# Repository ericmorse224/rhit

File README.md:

Rose-Hulman Institute of Technology (RHIT) github contains all of the work, except ECE230 and ECE434 class, in individual branches within RHIT main branch.
I moved all branches into individual folders for better organization.

ECE230 folder is Embedded C code from Introduction to Embedded Systems class.

ECE310 folder is Matlab code from Communication Systems class.

ECE320 folder is Simulink and C code from Linear Controls class (some code was provided by professor to modify).

ECE333 folder is Verilog code from Embedded Systems class

ECE341 folder is Matlab code from Electromagnetic Fields class.

ECE380 folder is LabVIEW code from Discrete Time and Continuous Signals class.

MATLAB folder is Matlab code that I created while at Rose-Hulman.

PCB folder is PCB layout that I created at Rose-Hulman.

PspiceFiles folder is Orcad Pspice files that I created at Rose-Hulman.

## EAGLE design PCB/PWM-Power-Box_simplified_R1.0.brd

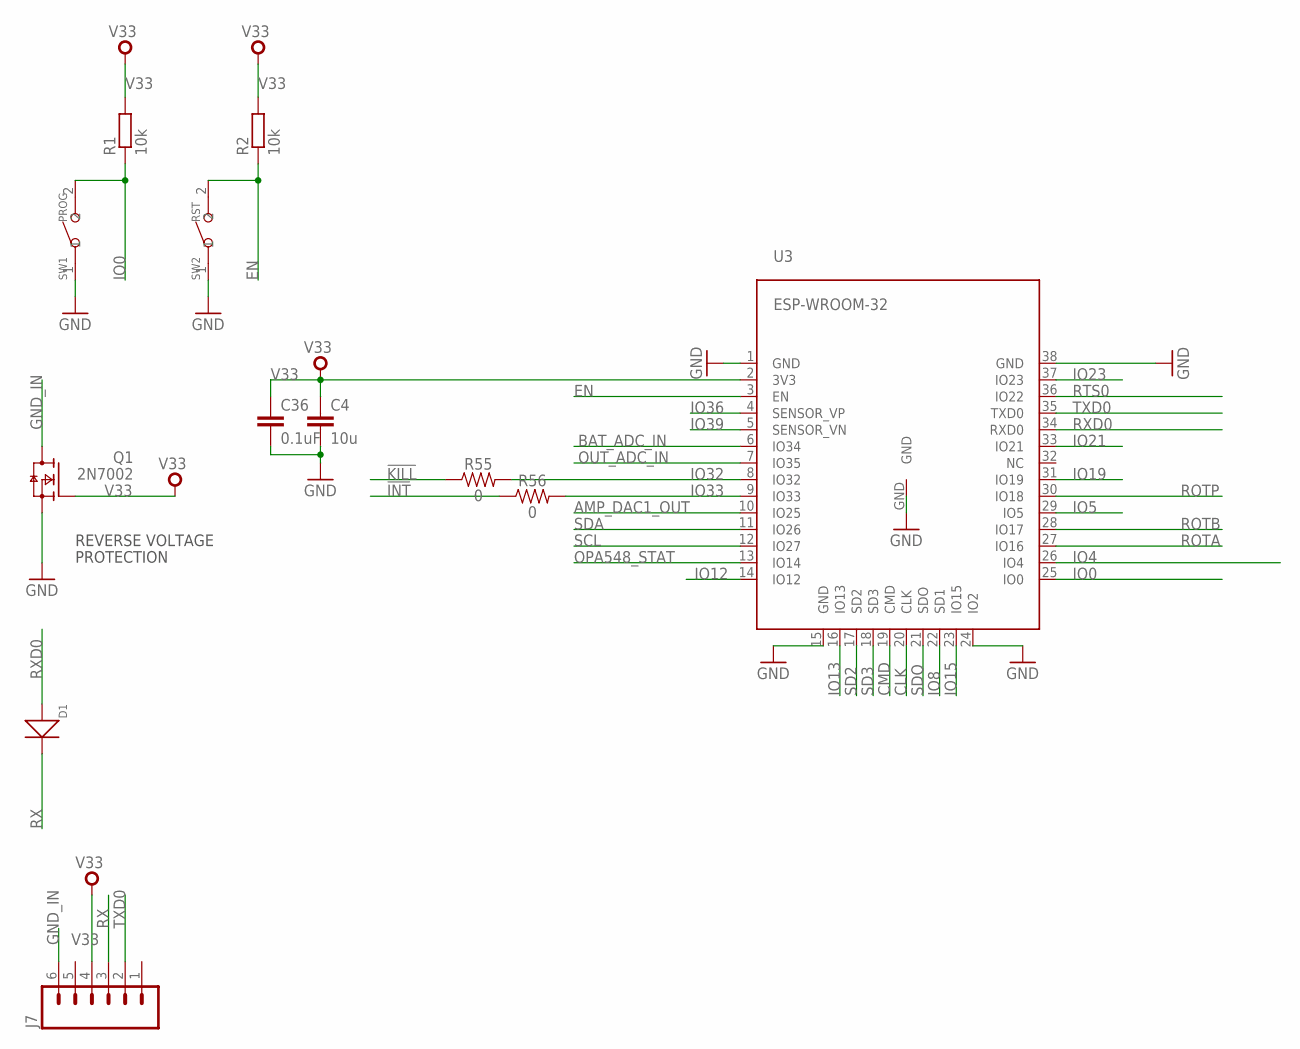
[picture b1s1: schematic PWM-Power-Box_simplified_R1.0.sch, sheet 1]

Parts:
C4: 10u; C0603
C36: 0.1uF; C0603
D1: DIODE'0805'; SOD-323
J7: M06SILK_FEMALE_PTH; 1X06
Q1: 2N7002; SOT23
R1, R2: 10k; R0603
R55, R56: 0; 0603
SW1: PROG; SW2-4.0-6.0X3.0X2.5MM
SW2: RST; SW2-4.0-6.0X3.0X2.5MM
U3: ESP-WROOM-32

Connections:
!INT: R56.1; also elsewhere on the board
!KILL: R55.1; also elsewhere on the board
AMP_DAC1_OUT: U3.10 (IO25); also elsewhere on the board
BAT_ADC_IN: U3.6 (IO34); also elsewhere on the board
CLK: U3.20 (CLK)
CMD: U3.19 (CMD)
EN: R2.1, SW2.2, U3.3 (EN); also elsewhere on the board
GND: C4.2, C36.2, Q1.2 (S), SW1.1, SW2.1, U3.1 (GND), U3.15 (GND), U3.24 (IO2), U3.38 (GND), U3.GND; also elsewhere on the board
GND_IN: J7.6, Q1.3 (D)
IO0: R1.1, SW1.2, U3.25 (IO0); also elsewhere on the board
IO4: U3.26 (IO4)
IO5: U3.29 (IO5)
IO8: U3.22 (SD1)
IO12: U3.14 (IO12)
IO13: U3.16 (IO13)
IO15: U3.23 (IO15)
IO19: U3.31 (IO19)
IO21: U3.33 (IO21)
IO23: U3.37 (IO23)
IO32: R55.2, U3.8 (IO32)
IO33: R56.2, U3.9 (IO33)
IO36: U3.4 (SENSOR_VP)
IO39: U3.5 (SENSOR_VN)
OPA548_STAT: U3.13 (IO14); also elsewhere on the board
OUT_ADC_IN: U3.7 (IO35); also elsewhere on the board
ROTA: U3.27 (IO16); also elsewhere on the board
ROTB: U3.28 (IO17); also elsewhere on the board
ROTP: U3.30 (IO18); also elsewhere on the board
RTS0: U3.36 (IO22)
RX: D1.-, J7.3
RXD0: D1.+, U3.34 (RXD0); also elsewhere on the board
SCL: U3.12 (IO27); also elsewhere on the board
SD2: U3.17 (SD2)
SD3: U3.18 (SD3)
SDA: U3.11 (IO26); also elsewhere on the board
SDO: U3.21 (SDO)
TXD0: J7.2, U3.35 (TXD0); also elsewhere on the board
V33: C4.1, C36.1, J7.4, Q1.1 (G), R1.2, R2.2, U3.2 (3V3); also elsewhere on the board

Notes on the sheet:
REVERSE VOLTAGE
PROTECTION

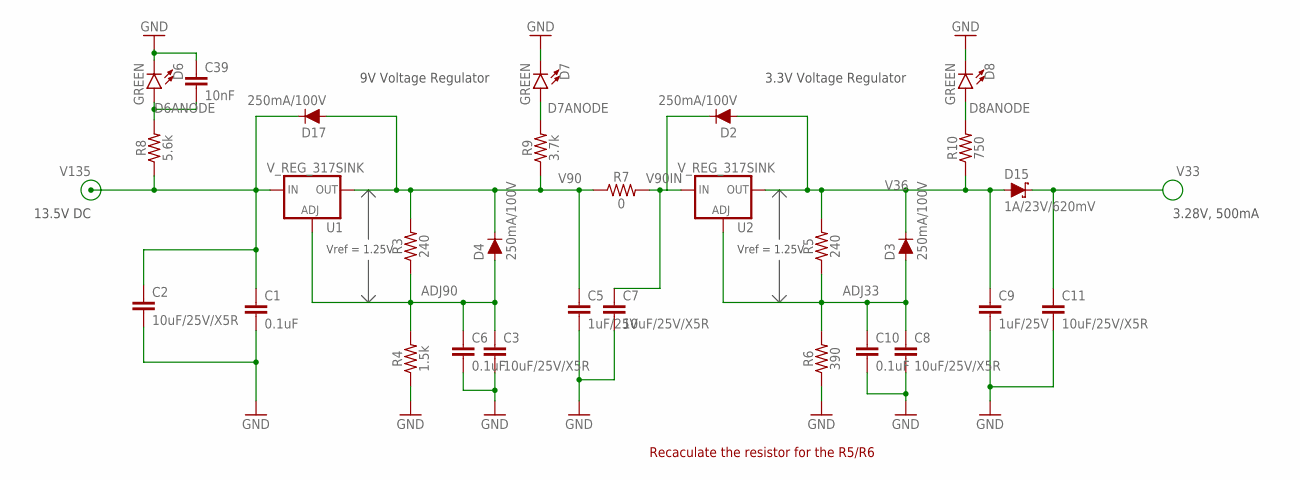
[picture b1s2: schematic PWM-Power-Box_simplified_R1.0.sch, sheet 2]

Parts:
C1: 0.1uF; C0805K
C2, C7, C11: 10uF/25V/X5R; C1210K
C3: 10uF/25V/X5R; C0805
C5, C9: 1uF/25V; C0805K
C6, C10: 0.1uF; C0603
C8: 10uF/25V/X5R; C0603
C39: 10nF; C0603
D2, D3, D4, D17: 250mA/100V; SOD-323
D6, D7, D8: GREEN; LED-0603
D15: 1A/23V/620mV; SOD-323
R3, R5: 240; 0603
R4: 1.5k; 0603
R6: 390; 0603
R7: 0; 1210
R8: 5.6k; 0603
R9: 3.7k; 0603
R10: 750; 0603
U1, U2: V_REG_317SINK; TO220-ADJ

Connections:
GND: C1.2, C2.2, C3.2, C5.2, C6.2, C7.2, C8.2, C9.2, C10.2, C11.2, C39.1, D6.C, D7.C, D8.C, R4.1, R6.1; also elsewhere on the board
unnamed: C3.1, C6.1, D4.A, R3.1, R4.2, U1.ADJ
unnamed: C8.1, C10.1, D3.A, R5.1, R6.2, U2.ADJ
unnamed: C7.1, D2.C, R7.2, U2.IN
unnamed: C39.2, D6.A, R8.2
unnamed: D7.A, R9.2
unnamed: D8.A, R10.2
V33: C11.1, D15.C; also elsewhere on the board
V36: C9.1, D2.A, D3.C, D15.A, R5.2, R10.1, U2.OUT
V90: C5.1, D4.C, D17.A, R3.2, R7.1, R9.1, U1.OUT
V135: C1.1, C2.1, D17.C, R8.1, U1.IN; also elsewhere on the board

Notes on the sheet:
9V Voltage Regulator
13.5V DC
Vref = 1.25V
3.3V Voltage Regulator
3.28V, 500mA
Recaculate the resistor for the R5/R6

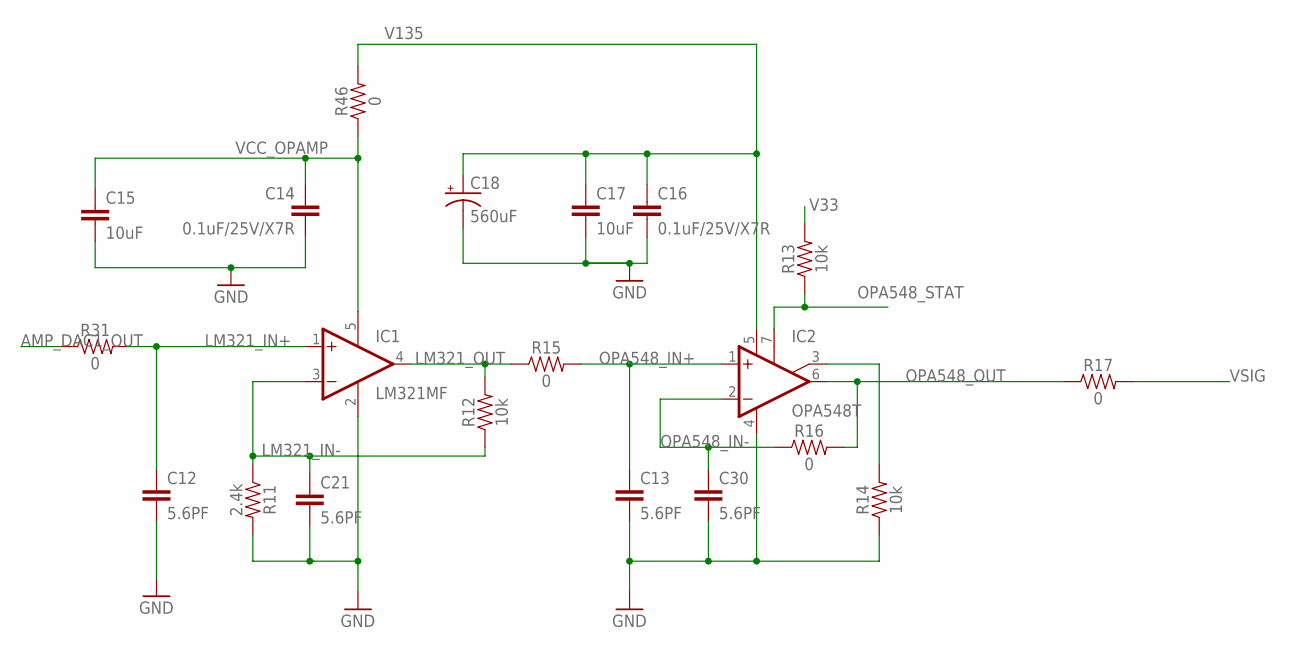
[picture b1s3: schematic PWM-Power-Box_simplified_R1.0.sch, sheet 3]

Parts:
C12, C13, C21, C30: 5.6PF; 0603
C14, C16: 0.1uF/25V/X7R; 0603
C15, C17: 10uF; 1206
C18: 560uF; PANASONIC_G
IC1: LM321MF; SOT23-5
IC2: OPA548T; TO220-7
R11: 2.4k; 0603
R12, R13, R14: 10k; 0603
R15, R16, R31, R46: 0; 0603
R17: 0; 1210

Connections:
AMP_DAC1_OUT: R31.1; also elsewhere on the board
GND: C12.2, C13.2, C14.2, C15.2, C16.2, C17.2, C18.-, C21.2, C30.2, IC1.2 (V-), IC2.4 (V-), R11.2, R14.1; also elsewhere on the board
LM321_IN+: C12.1, IC1.1 (+IN), R31.2
LM321_IN-: C21.1, IC1.3 (-IN), R11.1, R12.1
LM321_OUT: IC1.4 (OUT), R12.2, R15.1
unnamed: IC2.3 (ILIM), R14.2
OPA548_IN+: C13.1, IC2.1 (+IN), R15.2
OPA548_IN-: C30.1, IC2.2 (-IN), R16.1
OPA548_OUT: IC2.6 (OUT), R16.2, R17.1; also elsewhere on the board
OPA548_STAT: IC2.7 (E/S), R13.1; also elsewhere on the board
V33: R13.2; also elsewhere on the board
V135: C16.1, C17.1, C18.+, IC2.5 (V+), R46.2; also elsewhere on the board
VCC_OPAMP: C14.1, C15.1, IC1.5 (V+), R46.1
VSIG: R17.2; also elsewhere on the board

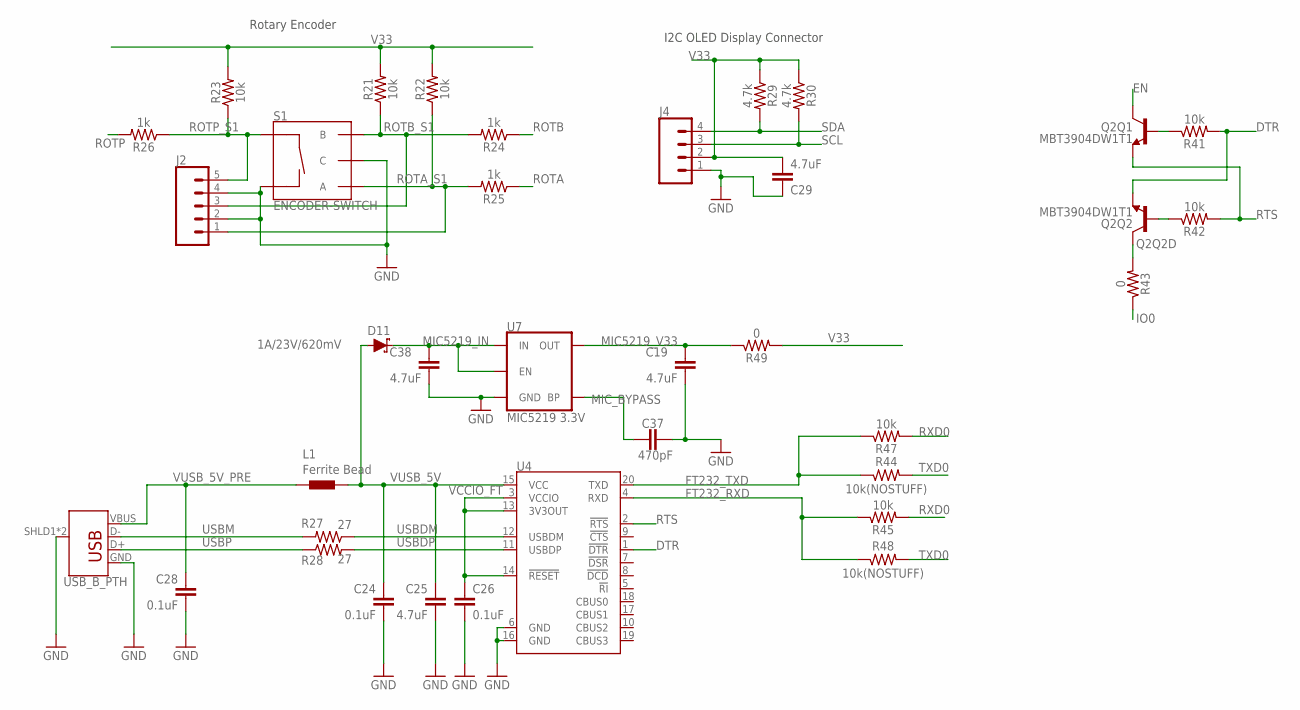
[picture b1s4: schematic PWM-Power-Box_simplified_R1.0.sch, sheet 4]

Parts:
C19, C25, C29, C38: 4.7uF; 0603
C24, C26, C28: 0.1uF; 0603
C37: 470pF; 0603
D11: 1A/23V/620mV; SOD-323
J2: CONN_05; 1X05
J3: USB_B_PTH; USB-B-PTH
J4: CONN_04; 1X04
L1: Ferrite Bead; 0402
Q2: MBT3904DW1T1; SC70-6
R21, R22, R23, R41, R42, R45, R47: 10k; 0603
R24, R25, R26: 1k; 0603
R27, R28: 27; 0603
R29, R30: 4.7k; 0603
R43, R49: 0; 0603
R44, R48: 10k(NOSTUFF); 0603
S1: ENCODER-SWITCH; ROTARY_ENC_PLAIN
U4: FT231XS; SSOP20_L
U7: MIC5219 3.3V; SOT23-5

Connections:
DTR: Q2.1 (E), R41.2, U4.1 (!DTR)
EN: Q2.3 (C); also elsewhere on the board
FT232_RXD: R45.1, R48.1, U4.4 (RXD)
FT232_TXD: R44.1, R47.1, U4.20 (TXD)
GND: C19.2, C24.2, C25.2, C26.2, C28.2, C29.1, C37.2, C38.2, J2.2, J2.4, J3.GND, J3.SHLD1 (SHIELD), J3.SHLD2 (SHIELD), J4.1, S1.C, S1.SW-, U4.6 (GND), U4.16 (GND), U7.2 (GND); also elsewhere on the board
IO0: R43.1; also elsewhere on the board
MIC5219_IN: C38.1, D11.C, U7.1 (IN), U7.3 (EN)
MIC5219_V33: C19.1, R49.1, U7.5 (OUT)
unnamed: C37.1, U7.4 (BP)
unnamed: J2.5, R23.1, R26.1, S1.SW+
unnamed: J2.3, R21.1, R24.2, S1.B
unnamed: J2.1, R22.1, R25.2, S1.A
unnamed: C26.1, U4.3 (VCCIO), U4.13 (3V3OUT), U4.14 (!RESET)
unnamed: R27.1, U4.12 (USBDM)
unnamed: R28.2, U4.11 (USBDP)
unnamed: J3.D+, R28.1
unnamed: J3.D-, R27.2
unnamed: Q2.5 (B), R41.1
unnamed: Q2.2 (B), R42.1
unnamed: Q2.6 (C), R43.2
ROTA: R25.1; also elsewhere on the board
ROTB: R24.1; also elsewhere on the board
ROTP: R26.2; also elsewhere on the board
RTS: Q2.4 (E), R42.2, U4.2 (!RTS)
RXD0: R45.2, R47.2; also elsewhere on the board
SCL: J4.3, R30.2; also elsewhere on the board
SDA: J4.4, R29.2; also elsewhere on the board
TXD0: R44.2, R48.2; also elsewhere on the board
V33: C29.2, J4.2, R21.2, R22.2, R23.2, R29.1, R30.1, R49.2; also elsewhere on the board
VUSB_5V: C24.1, C25.1, D11.A, L1.2, U4.15 (VCC)
VUSB_5V_PRE: C28.1, J3.VBUS, L1.1

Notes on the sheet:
Rotary Encoder
I2C OLED Display Connector

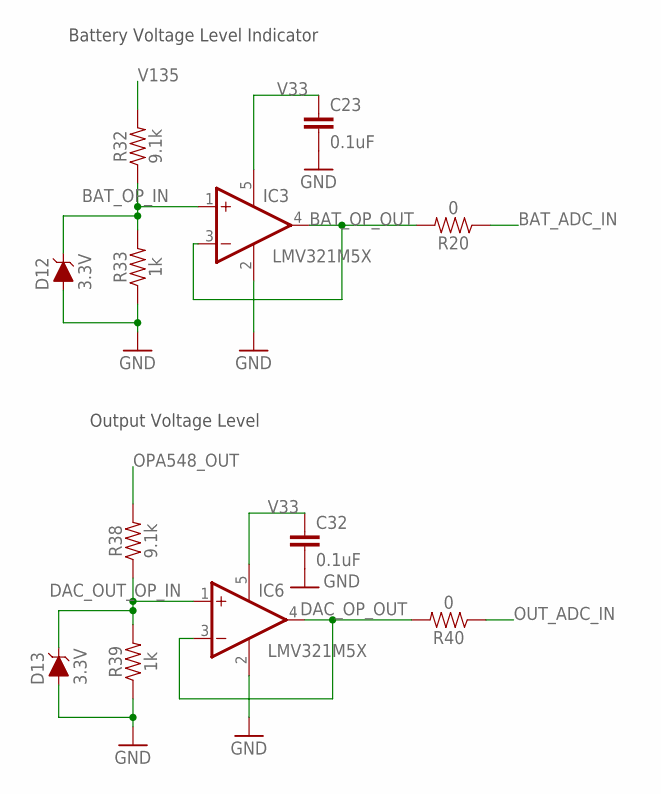
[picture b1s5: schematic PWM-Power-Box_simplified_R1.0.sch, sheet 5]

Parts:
C23, C32: 0.1uF; 0603
D12, D13: 3.3V; SOD-323
IC3, IC6: LMV321M5X; SOT23-5
R20, R40: 0; 0603
R32, R38: 9.1k; 0603
R33, R39: 1k; 0603

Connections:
BAT_ADC_IN: R20.1; also elsewhere on the board
BAT_OP_IN: D12.C, IC3.1 (+IN), R32.1, R33.2
BAT_OP_OUT: IC3.3 (-IN), IC3.4 (OUT), R20.2
DAC_OP_OUT: IC6.3 (-IN), IC6.4 (OUT), R40.2
DAC_OUT_OP_IN: D13.C, IC6.1 (+IN), R38.1, R39.2
GND: C23.2, C32.2, D12.A, D13.A, IC3.2 (V-), IC6.2 (V-), R33.1, R39.1; also elsewhere on the board
OPA548_OUT: R38.2; also elsewhere on the board
OUT_ADC_IN: R40.1; also elsewhere on the board
V33: C23.1, C32.1, IC3.5 (V+), IC6.5 (V+); also elsewhere on the board
V135: R32.2; also elsewhere on the board

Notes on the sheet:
Battery Voltage Level Indicator
Output Voltage Level

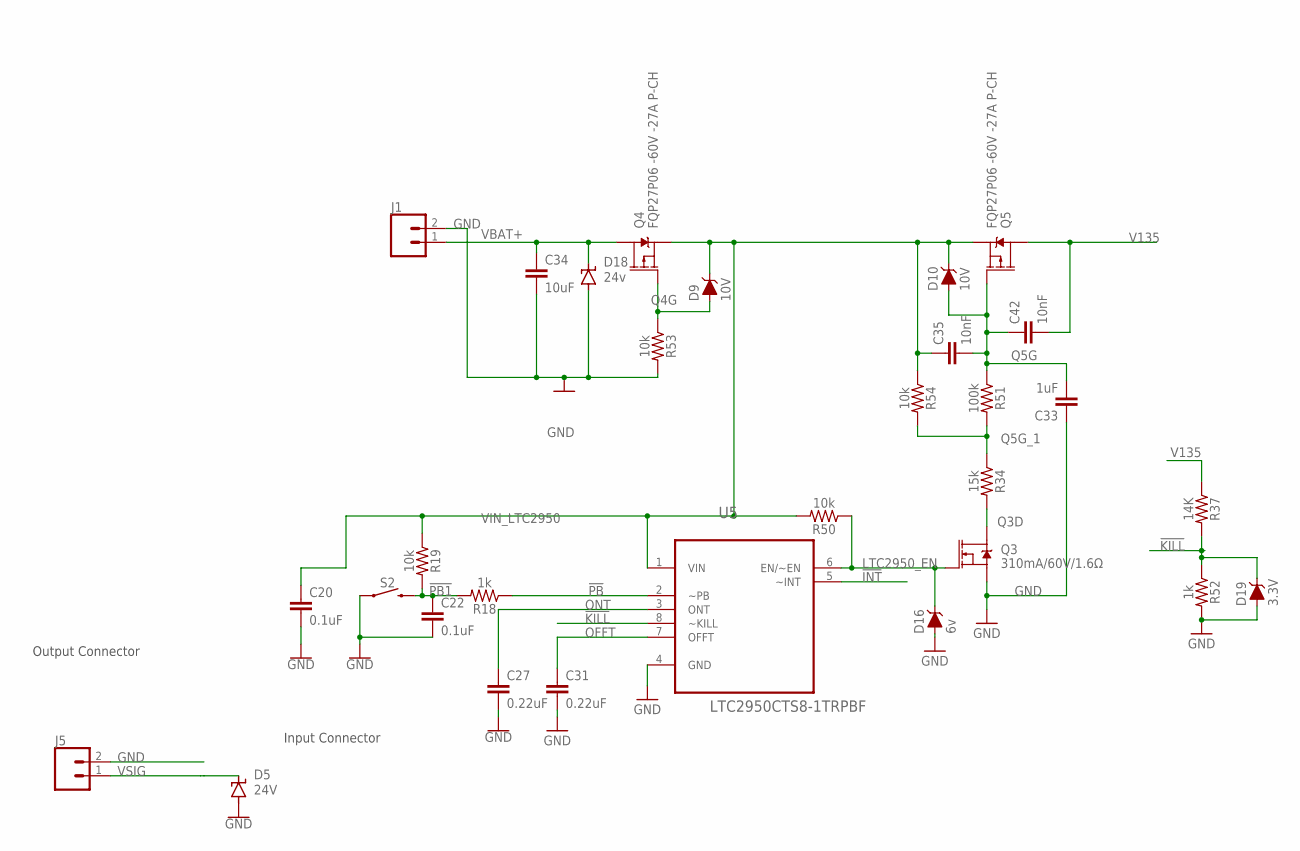
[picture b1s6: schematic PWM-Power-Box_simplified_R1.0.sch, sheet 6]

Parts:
C20, C22: 0.1uF; 0603
C27, C31: 0.22uF; 0603
C33: 1uF; 0603
C34: 10uF; 1210
C35, C42: 10nF; 0603
D5: 24V; SMBG
D9, D10: 10V; SOD-323
D16: 6v; SOD-323
D18: 24v; SMBG
D19: 3.3V; SOD-323
J1, J5: CONN_025MM; SCREWTERMINAL-5MM-2
Q3: 310mA/60V/1.6Ω; SOT323
Q4, Q5: FQP27P06 -60V -27A P-CH; TO220V
R18, R52: 1k; 0603
R19, R50, R53, R54: 10k; 0603
R34: 15k; 0603
R37: 14K; 0603
R51: 100k; 0603
S2: MOMENTARY-SWITCH-SPST-PTH-RIGHT-ANGLE-KIT; TACTILE_SWITCH_PTH_RIGHT_ANGLE_KIT
U5: LTC2950CTS8-1TRPBF; SOT65P280X100-8N

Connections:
!INT: U5.5 (~INT); also elsewhere on the board
!KILL: D19.C, R37.2, R52.1, U5.8 (~KILL); also elsewhere on the board
!PB: R18.1, U5.2 (~PB)
!PB1: C22.1, R18.2, R19.2, S2.2
GND: C20.2, C22.2, C27.2, C31.2, C33.1, C34.2, D5.A, D16.A, D18.A, D19.A, J1.2, J5.2, Q3.2 (S), R52.2, R53.2, S2.1, U5.4 (GND); also elsewhere on the board
LTC2950_EN: D16.C, Q3.1 (G), R50.1, U5.6 (EN/~EN)
unnamed: C33.2, C35.2, C42.1, D10.A, Q5.1 (G), R51.1
unnamed: D9.A, Q4.1 (G), R53.1
unnamed: Q3.3 (D), R34.2
OFFT: C31.1, U5.7 (OFFT)
ONT: C27.1, U5.3 (ONT)
Q3D: R34.1, R51.2, R54.2
V135: C42.2, Q5.2 (D), R37.1; also elsewhere on the board
VBAT+: C34.1, D18.C, J1.1, Q4.2 (D)
VIN_LTC2950: C20.1, C35.1, D9.C, D10.C, Q4.3 (S), Q5.3 (S), R19.1, R50.2, R54.1, U5.1 (VIN)
VSIG: D5.C, J5.1; also elsewhere on the board

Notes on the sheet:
Input Connector
Output Connector

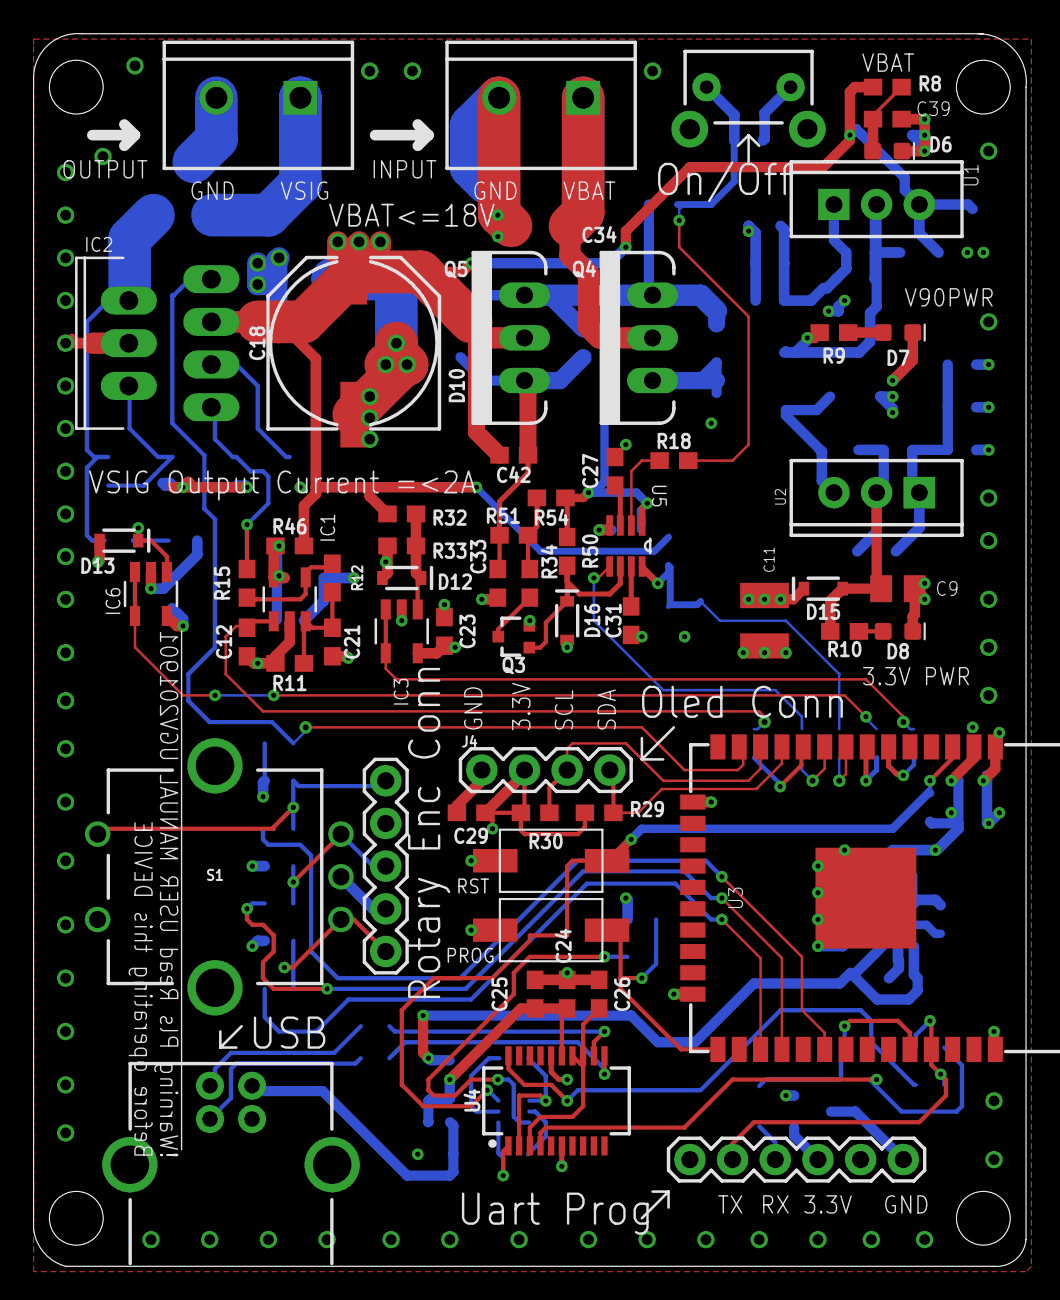
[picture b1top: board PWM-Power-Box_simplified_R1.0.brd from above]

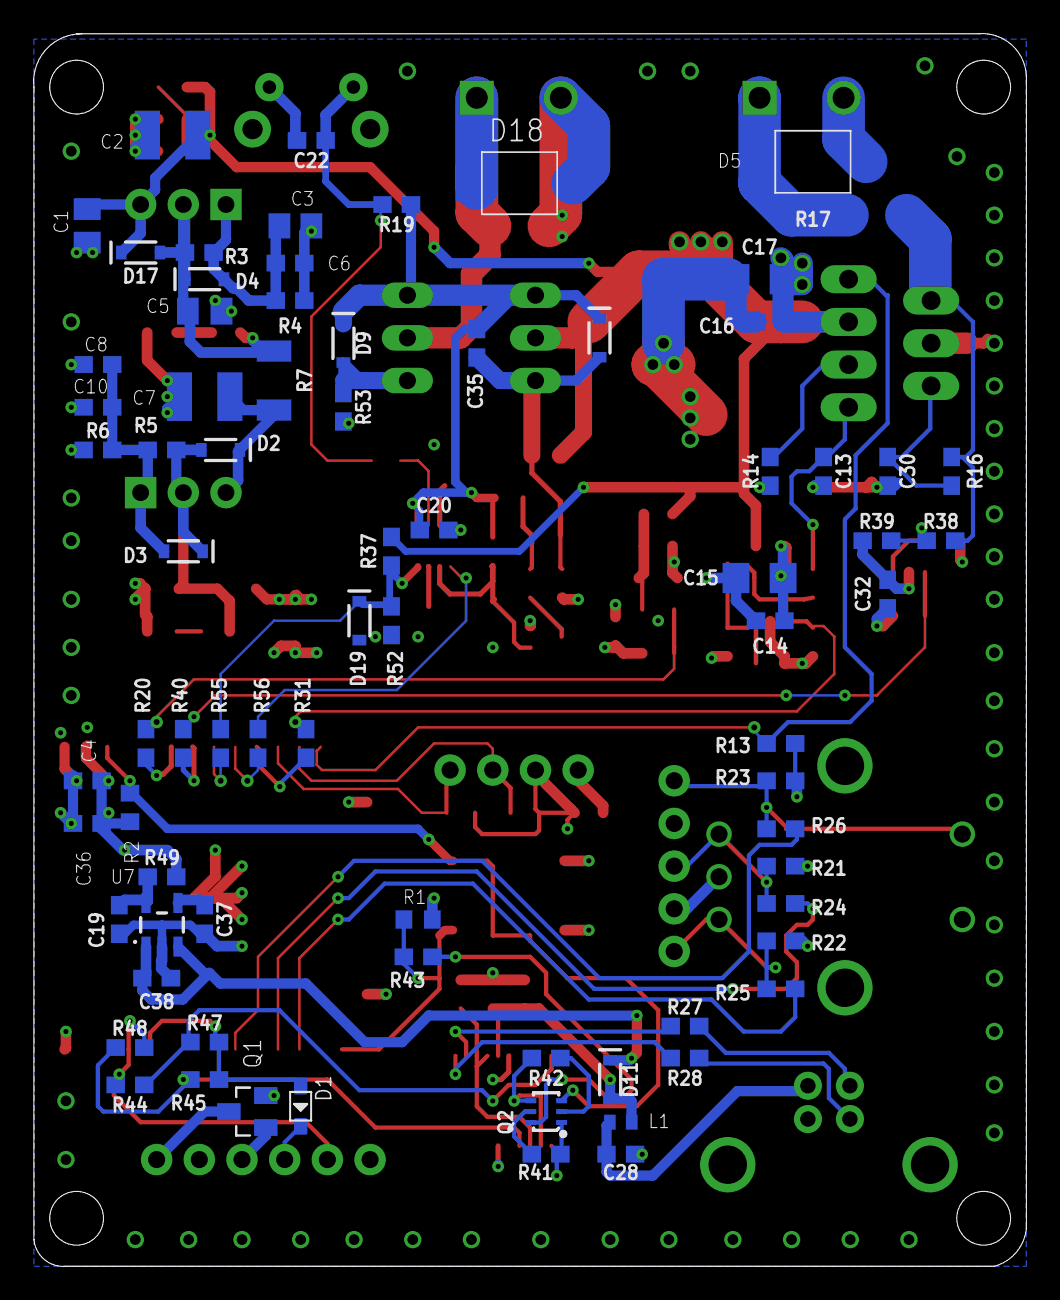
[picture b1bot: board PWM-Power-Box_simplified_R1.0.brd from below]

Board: 4 copper layers, 59.1 x 73.4 mm, 138 parts (77 on the bottom side), 74 nets.

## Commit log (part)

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2025-04-25 Filter response experiment from ECE320
    Filter response experiment from ECE320 class at RHIT with team: Rahul Das and Eric Morse
2025-04-25 ECE310 work on Communication Systems class
    ECE310 work on Communication Systems class
2025-04-25 Matlab code for Electromagnetic Waves class
    Matlab code developed for the Electromagnetic Waves class.
2025-04-25 LabView code developed for RHIT ECE380 class
    LabView code developed for RHIT ECE380 Discrete Time and Continuous Signals class
2025-04-25 PCB work
    PCB work done at Rose-Hulman Institute of Technology
2025-11-19 Update README.md
    formatted and improved README.md
2025-11-19 Update README.md
    Updated README.md

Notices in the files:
parts and their libraries:
SparkFun-Capacitors: Licensing: Creative Commons ShareAlike 4.0 International - https://creativecommons.org/licenses/by-sa/4.0
